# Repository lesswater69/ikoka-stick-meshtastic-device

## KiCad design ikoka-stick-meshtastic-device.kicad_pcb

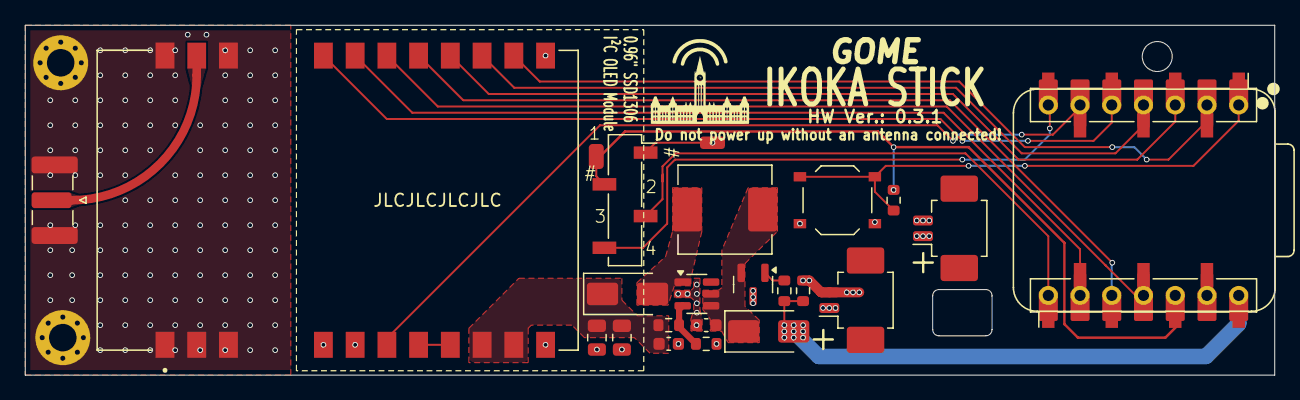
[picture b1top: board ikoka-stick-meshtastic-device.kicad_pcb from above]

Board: 2 copper layers, 100.0 x 28.0 mm, 27 parts (1 on the bottom side), 22 nets.

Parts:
BT1: Battery_Cell; BatteryHolder_MYOUNG_BH-21700-B1BJ001_1x21700
C1, C2: 22uF; C_0603_1608Metric
C3, C4: 47uF; C_0805_2012Metric
D1, D3: SS34; D_SMA
H1, H2: MountingHole; MountingHole_2.2mm_M2_Pad_Via
J1: Conn_Coaxial; SMA_Samtec_SMA-J-P-H-ST-EM1_EdgeMount
J2, J3: Conn_01x07_Socket; PinSocket_1x07_P2.54mm_Vertical_SMD_Pin1Left
J4, J5: Conn_01x02; Molex_PicoBlade_53261-0271_1x02-1MP_P1.25mm_Horizontal
J6: Conn_01x04; PinSocket_1x04_P2.54mm_Vertical_SMD_Pin1Right
L1: 22uH; L_Sunlord_MWSA0624S
Q1: AO3401A; SOT-23
R1: 300K; R_0603_1608Metric
R2: 39K; R_0603_1608Metric
R3, R5: 100k; R_0603_1608Metric
R4: 1k; R_0603_1608Metric
SW1: SW_Push; SW_Push_1P1T_XKB_TS-1187A
U1: MT3608; SOT-23-6
U2: E22-900M30S; XCVR_E22-900M30S
U3: XIAO-ESP32-S3-SMD; XIAO-ESP32S3-DIP
pin1: SolderWirePad_1x01_SMD_1.5x3mm

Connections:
+3V3: J3.5, J6.2, R5.1, U3.12 (VCC_3V3), pin1.1
+5V: D3.2 (A), J3.7, R3.1, R4.1, U3.14 (VBUS)
+5V2_LORA: C2.1, C3.1, C4.1, D1.1 (K), R1.1, U2.9 (VCC), U2.10 (VCC)
+BATT: BT1.1 (+), J4.1, J5.1, Q1.3 (D)
/ANT: J1.1 (In), U2.21 (ANT)
/BOOST_IN: C1.1, D3.1 (K), L1.2, Q1.2 (S), U1.4 (EN), U1.5 (IN)
/D0: J2.1, R5.2, SW1.1, U3.1 (GPIO1/D0/A0)
/I2C_SCL: J3.1, J6.3, U3.8 (U0RXD/D7/RX)
/I2C_SDA: J2.7, J6.4, U3.7 (U0TXD/D6/TX)
/LORA_BUSY: J2.4, U2.14 (BUSY), U3.4 (GPIO4/D3/A3)
/LORA_DIO1: J2.2, U2.13 (DIO1), U3.2 (GPIO2/DA/A1)
/LORA_RST: J2.3, U2.15 (~RST), U3.3 (GPIO3/D2/A2)
/LORA_RXEN: J2.6, U2.6 (RXEN), U3.6 (GPIO9/D5/I2C_SCL)
/LORA_SPI_MISO: J3.3, U2.16 (MISO), U3.10 (GPIO8/D9/A9/MISO)
/LORA_SPI_MOSI: J3.4, U2.17 (MOSI), U3.11 (GPIO9/D10/A10/MOSI)
/LORA_SPI_NSS: J2.5, U2.19 (NSS), U3.5 (GPIO5/D4/I2C_SDA)
/LORA_SPI_SCK: J3.2, U2.18 (SCK), U3.9 (GPIO7/D8/A8/SCK)
GND: BT1.2 (-), C1.2, C2.2, C3.2, C4.2, H1.1, H2.1, J1.2 (Ext), J3.6, J4.2, J5.2, J6.1, R2.2, R3.2, SW1.2, U1.2 (GND), U2.1 (GND), U2.2 (GND), U2.3 (GND), U2.4 (GND), U2.5 (GND), U2.11 (GND), U2.12 (GND), U2.20 (GND), U2.22 (GND), U3.13 (GND)
unnamed: D1.2 (A), L1.1, U1.1 (SW)
unnamed: Q1.1 (G), R4.2
unnamed: R1.2, R2.1, U1.3 (FB)
unnamed: U2.7 (TXEN), U2.8 (DIO2)

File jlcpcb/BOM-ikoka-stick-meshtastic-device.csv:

Comment,Designator,Footprint,LCSC,Quantity
100k,"R3,R5",R_0603_1608Metric,C25803,2
1k,R4,R_0603_1608Metric,C21190,1
22uF,"C1,C2",C_0603_1608Metric,C59461,2
22uH,L1,L_Sunlord_MWSA0624S,C408436,1
300K,R1,R_0603_1608Metric,C23024,1
39K,R2,R_0603_1608Metric,C23153,1
47uF,"C3,C4",C_0805_2012Metric,C16780,2
AO3401A,Q1,SOT-23,C15127,1
Battery_Cell,BT1,BatteryHolder_MYOUNG_BH-21700-B1BJ001_1x21700,C20606791,1
Conn_01x02,"J4,J5",Molex_PicoBlade_53261-0271_1x02-1MP_P1.25mm_Horizontal,C2905009,2
Conn_01x04,J6,PinSocket_1x04_P2.54mm_Vertical_SMD_Pin1Right,C46635840,1
Conn_01x07_Socket,"J2,J3",PinSocket_1x07_P2.54mm_Vertical_SMD_Pin1Left,C42379199,2
Conn_Coaxial,J1,SMA_Samtec_SMA-J-P-H-ST-EM1_EdgeMount,C5250058,1
E22-900M30S,U2,XCVR_E22-900M30S,C411294,1
MT3608,U1,SOT-23-6,C2932326,1
SS34,"D1,D3",D_SMA,C8678,2
SW_Push,SW1,SW_Push_1P1T_XKB_TS-1187A,C318884,1

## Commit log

2025-10-02 Update ikoka-stick-meshtastic-device.kicad_pcb
    Silk screen edits to improve polarity awarness
2025-10-02 kicad export with silk screen changes
2025-10-21 pin_1_gnd
2025-10-21 rotation of q1,j1,j2,j3,j6 and bt1 adjustment
2025-10-22 version update, oled pinout silk
2026-01-12 replace OLED header with lower height variant
    https://www.lcsc.com/product-detail/C42379197.html
